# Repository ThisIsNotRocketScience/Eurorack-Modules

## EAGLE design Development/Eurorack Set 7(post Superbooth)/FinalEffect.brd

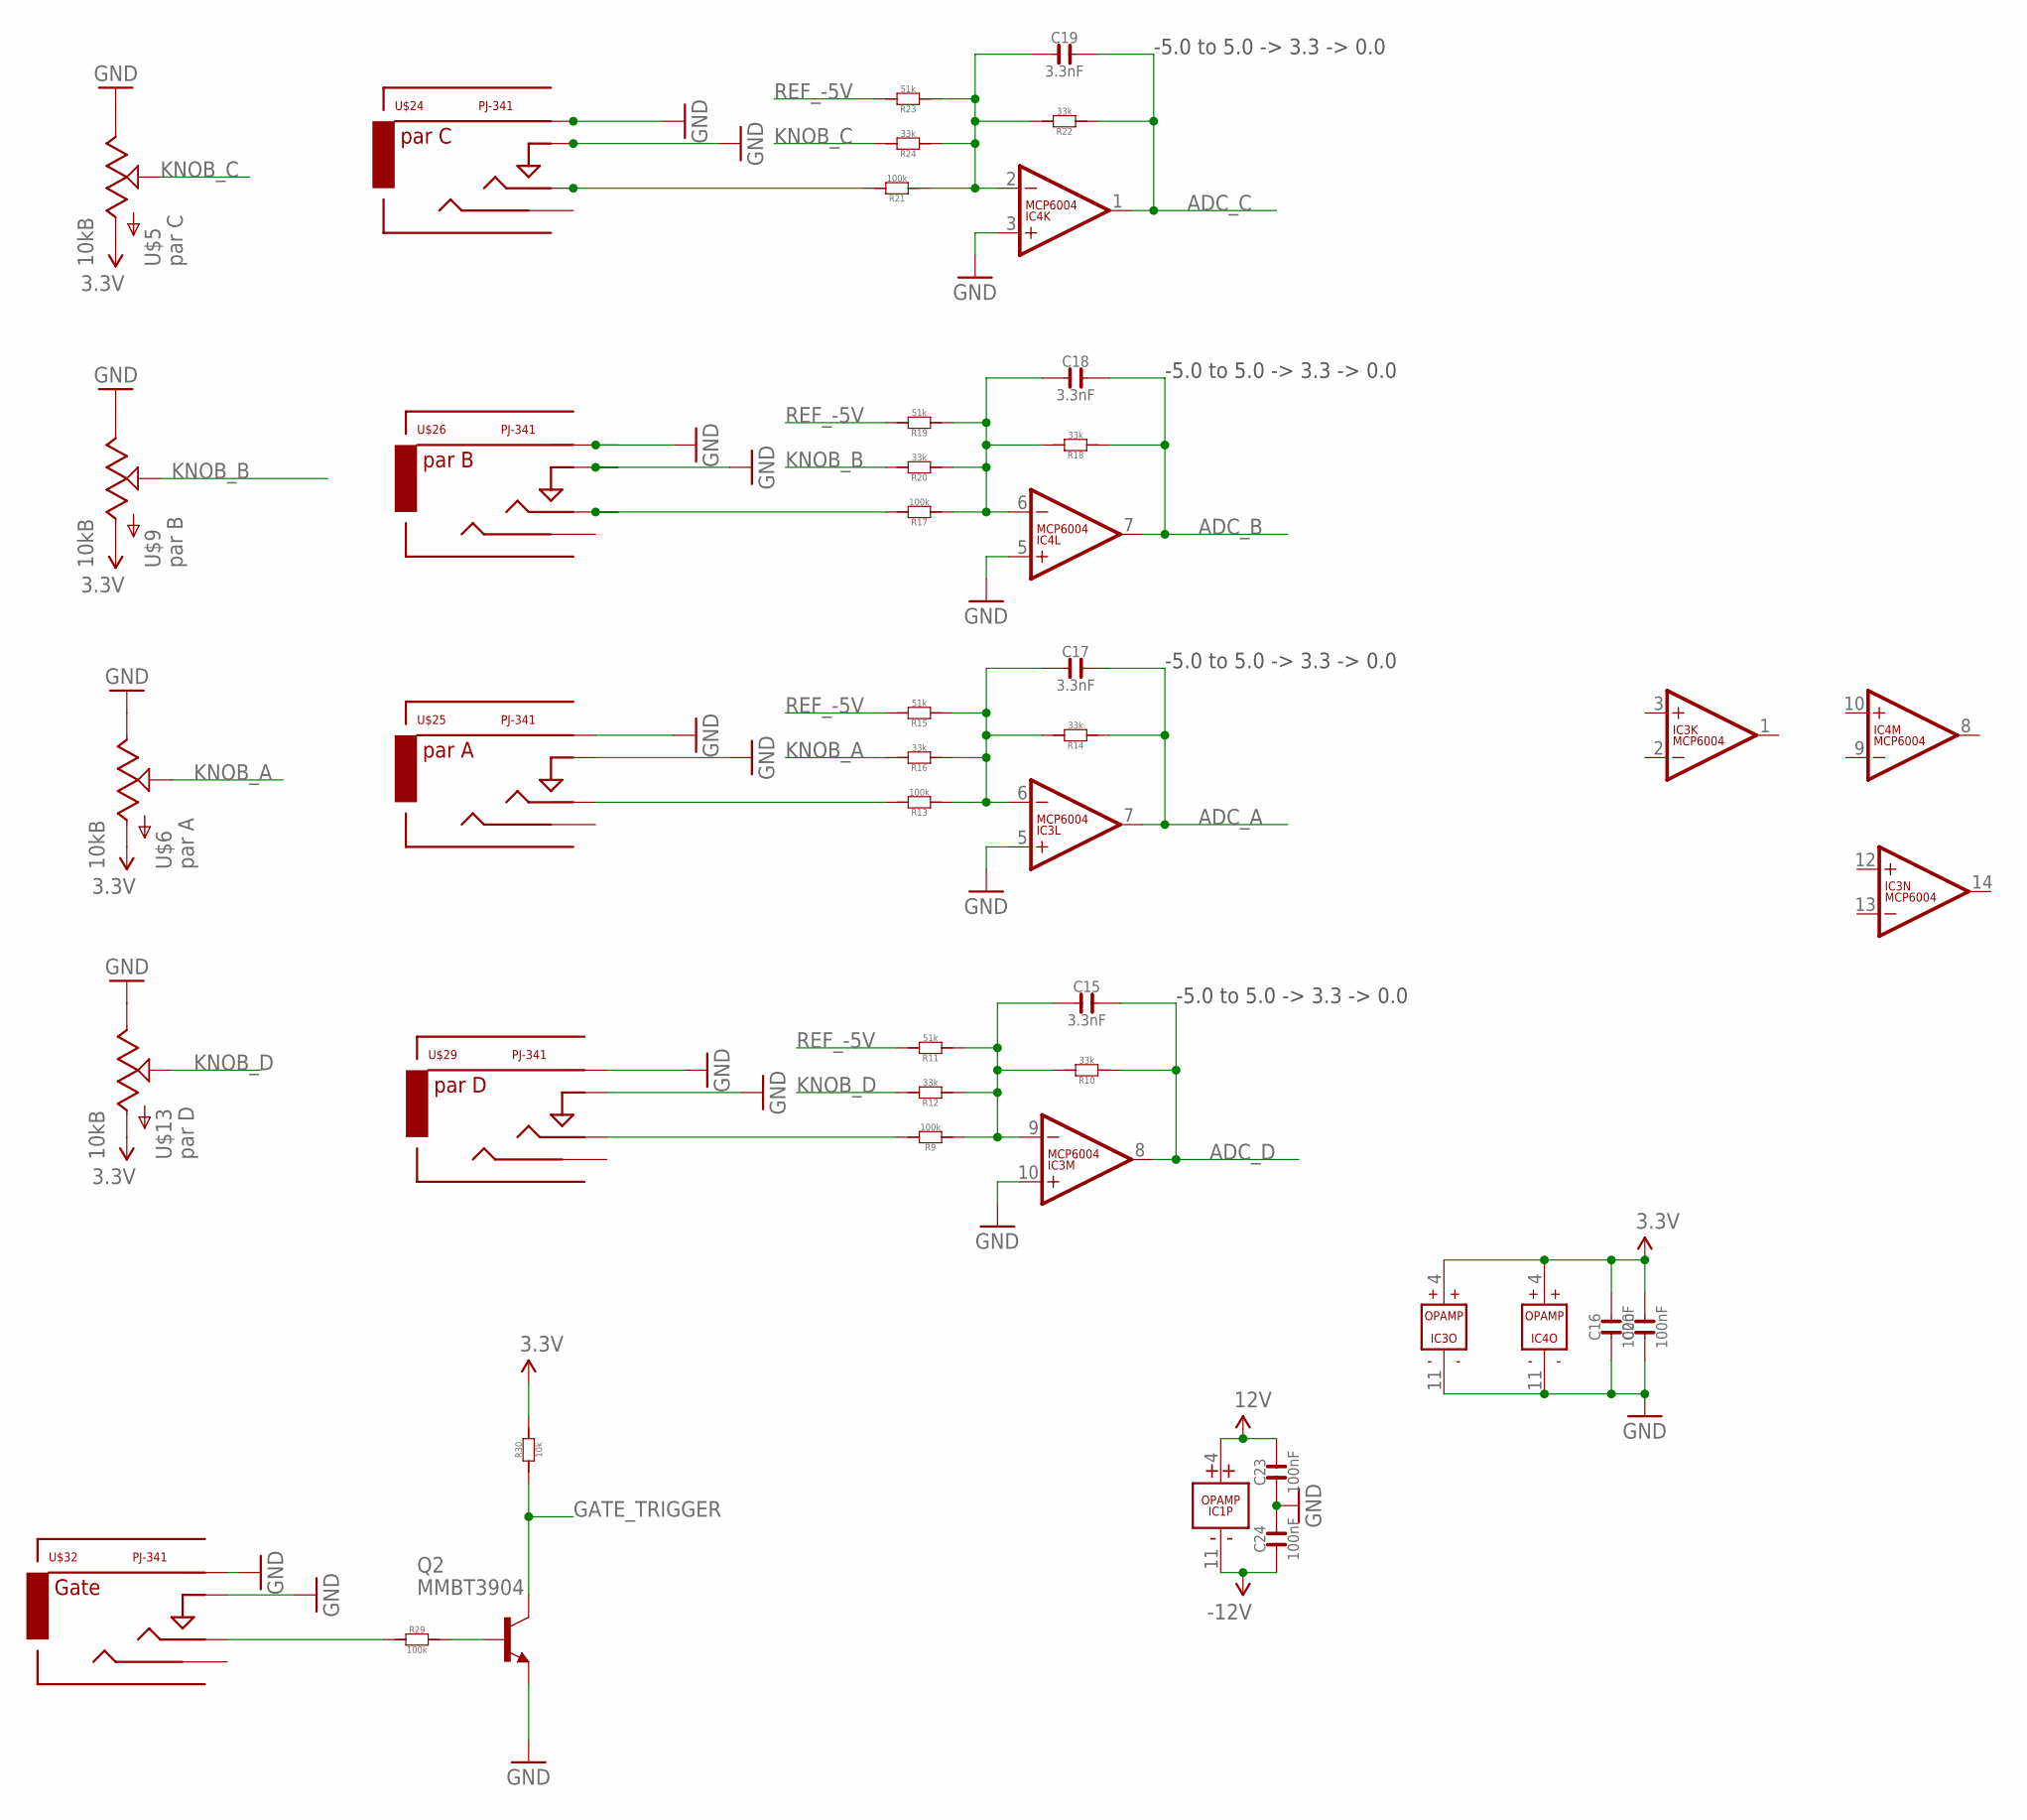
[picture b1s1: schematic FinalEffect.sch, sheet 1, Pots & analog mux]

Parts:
C15, C17, C18, C19: 3.3nF; C0603
C16, C20, C23, C24: 100nF; C0603
IC1: TL074D; SO14
IC3, IC4: MCP6004; SO14; MPN MCP6004-I/SL.
Q2: MMBT3904; SOT23-BEC; MPN PMBT3904,215
R9, R13, R17, R21, R29: 100k; R0603
R10, R12, R14, R16, R18, R20, R22, R24: 33k; R0603
R11, R15, R19, R23: 51k; R0603
R30: 10k; R0603
U$5, U$6, U$9, U$13: 10kB; OG-POTS_ALPS_POT_VERTICAL
U$24, U$25, U$26, U$29, U$32: PJ-341; 3.5MM-JACK-SWITCH-13MM-INPUT

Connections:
3.3V: C16.2, C20.2, IC3.4 (V+), IC4.4 (V+), R30.2, U$5.P$3 (A), U$6.P$3 (A), U$9.P$3 (A), U$13.P$3 (A); also elsewhere on the board
12V: C23.2, IC1.4 (V+); also elsewhere on the board
-12V: C24.1, IC1.11 (V-); also elsewhere on the board
ADC_A: C17.2, IC3.7 (OUT), R14.1; also elsewhere on the board
ADC_B: C18.2, IC4.7 (OUT), R18.1; also elsewhere on the board
ADC_C: C19.2, IC4.1 (OUT), R22.1; also elsewhere on the board
ADC_D: C15.2, IC3.8 (OUT), R10.1; also elsewhere on the board
GATE_TRIGGER: Q2.C, R30.1; also elsewhere on the board
GND: C16.1, C20.1, C23.1, C24.2, IC3.5 (+IN), IC3.10 (+IN), IC3.11 (V-), IC4.3 (+IN), IC4.5 (+IN), IC4.11 (V-), Q2.E, U$5.P$1 (E), U$6.P$1 (E), U$9.P$1 (E), U$13.P$1 (E), U$24.RING@3 (RING), U$24.SWITCH@3 (SWITCH), U$25.RING@3 (RING), U$25.SWITCH@3 (SWITCH), U$26.RING@3 (RING), U$26.SWITCH@3 (SWITCH), U$29.RING@3 (RING), U$29.SWITCH@3 (SWITCH), U$32.RING@3 (RING), U$32.SWITCH@3 (SWITCH); also elsewhere on the board
KNOB_A: R16.2, U$6.P$2 (S)
KNOB_B: R20.2, U$9.P$2 (S)
KNOB_C: R24.2, U$5.P$2 (S)
KNOB_D: R12.2, U$13.P$2 (S)
unnamed: R17.2, U$26.TIP@3 (TIP)
unnamed: C18.1, IC4.6 (-IN), R17.1, R18.2, R19.1, R20.1
unnamed: R21.2, U$24.TIP@3 (TIP)
unnamed: C19.1, IC4.2 (-IN), R21.1, R22.2, R23.1, R24.1
unnamed: Q2.B, R29.2
unnamed: R9.2, U$29.TIP@3 (TIP)
unnamed: C15.1, IC3.9 (-IN), R9.1, R10.2, R11.1, R12.1
unnamed: R13.2, U$25.TIP@3 (TIP)
unnamed: C17.1, IC3.6 (-IN), R13.1, R14.2, R15.1, R16.1
unnamed: R29.1, U$32.TIP@3 (TIP)
REF_-5V: R11.2, R15.2, R19.2, R23.2; also elsewhere on the board

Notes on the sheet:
-5.0 to 5.0 -> 3.3 -> 0.0

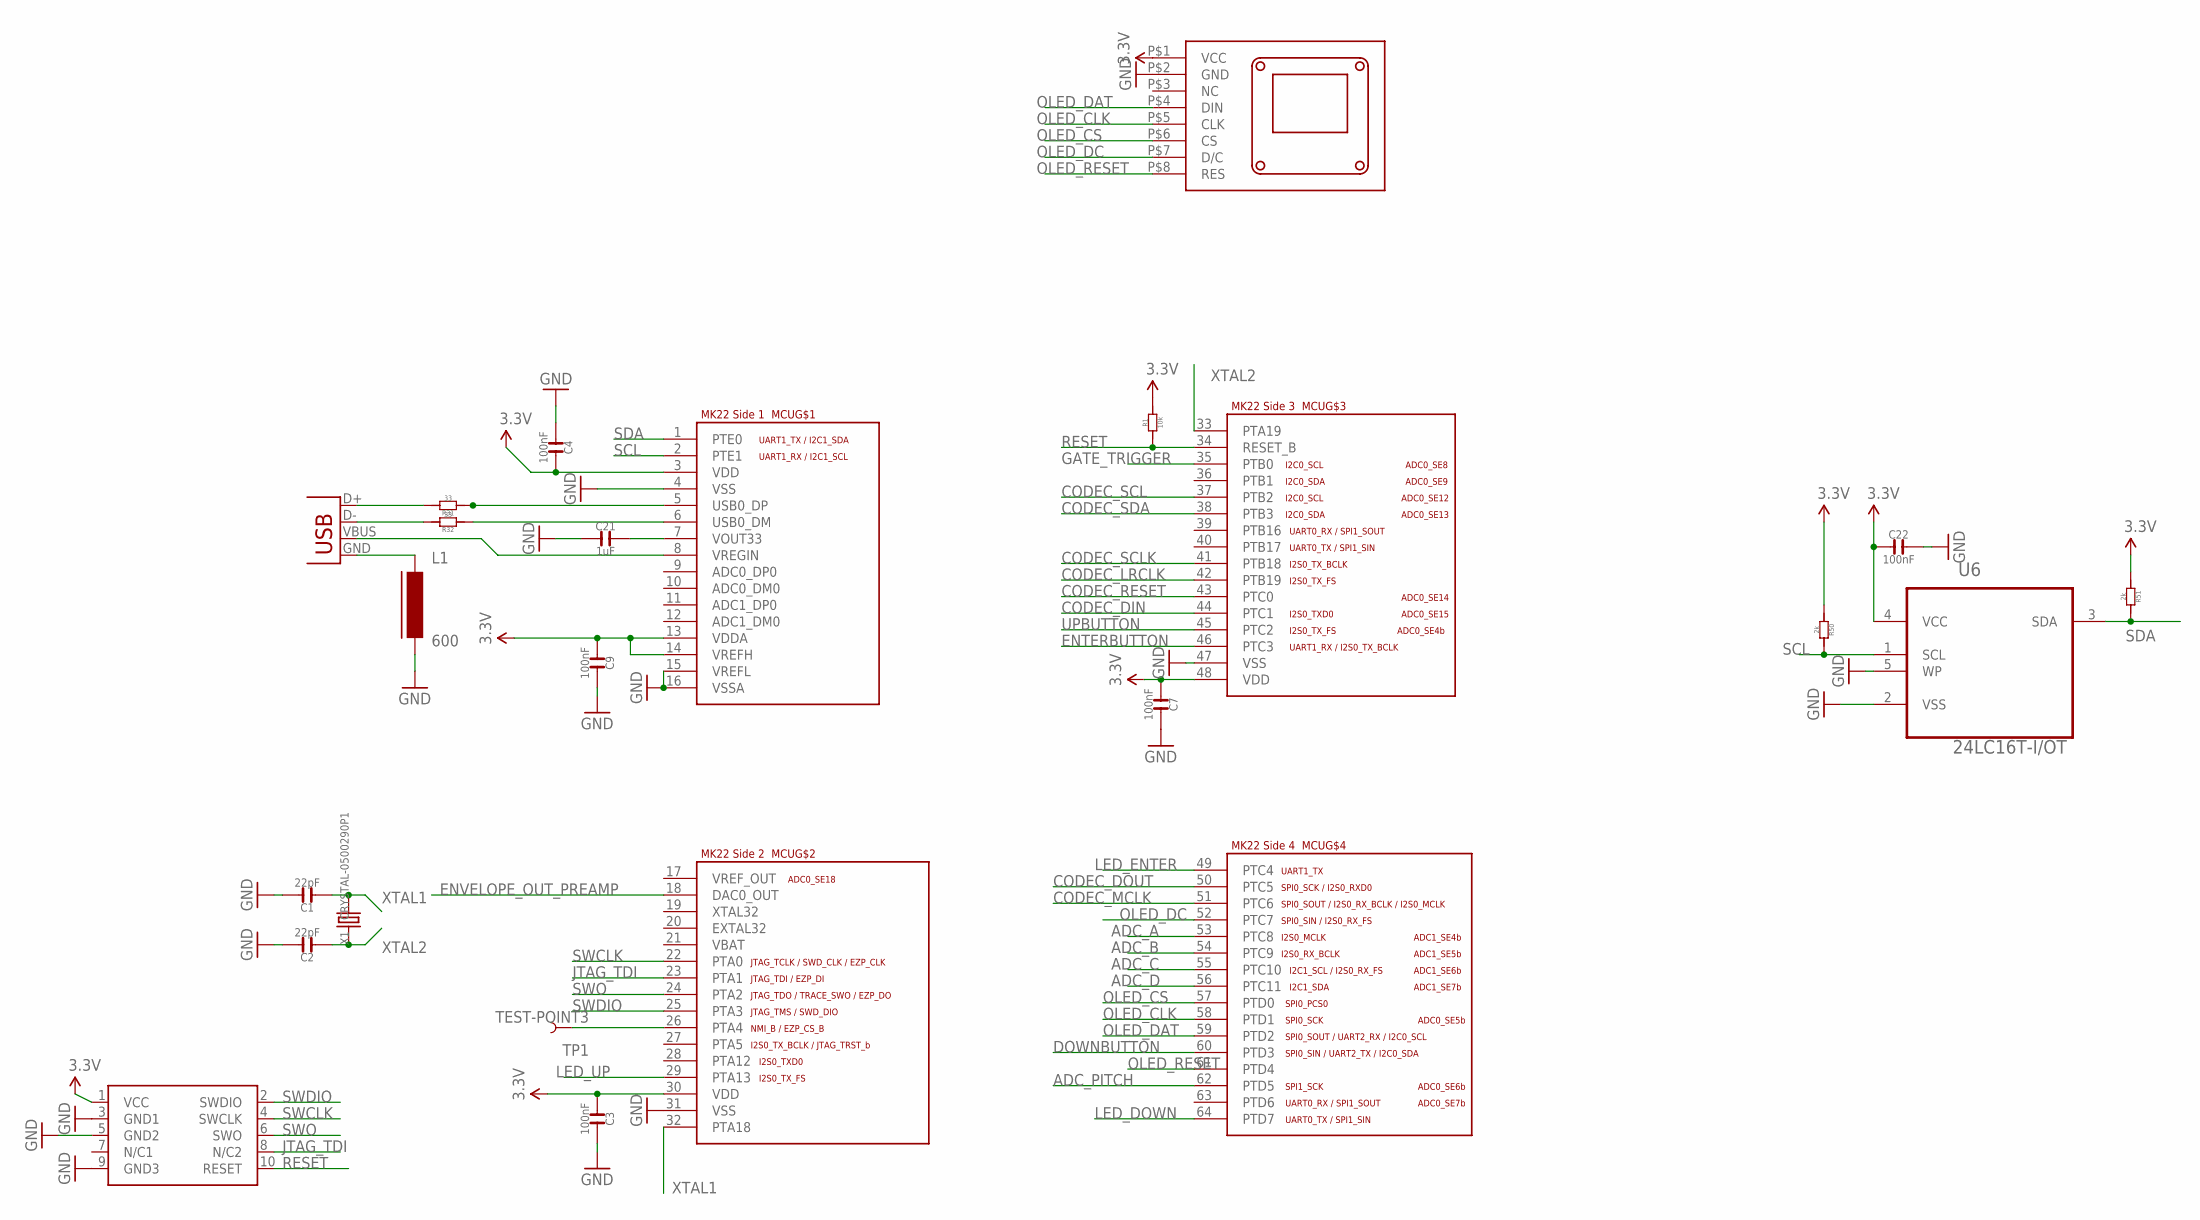
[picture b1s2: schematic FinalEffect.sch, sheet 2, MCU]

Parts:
C1, C2: 22pF; C0603
C3, C4, C7, C9, C22: 100nF; C0603
C21: 1uF; C0603
JP1: USBPTH-VERTICAL; USB-B-PTH-VERTICAL
L1: 600; FB603
MCU: MK22_120_TQFP64; MK22_TQFP64
R1: 10k; R0603
R31, R32: 33; R0603
R50, R51: 2k; R0603
SWD1: CORTEX_SWD; M50-3600542
TP1: TEST-POINT3; PAD.03X.03
U6: 24LC16T-I/OT; SOT95P290X145-5N; MPN 24LC00T-I/OT
U$3: 0.96OLEDMODULE; 1.3"OLEDMODULE
X1: CRYSTAL-0500290P1; 2P-SMD-5.0X3.2

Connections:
3.3V: C3.1, C4.2, C7.1, C9.1, C22.1, MCU.3 (VDD), MCU.13 (VDDA), MCU.14 (VREFH), MCU.30 (VDD), MCU.48 (VDD), R1.2, R50.1, R51.1, SWD1.1 (VCC), U6.4 (VCC), U$3.P$1 (VCC); also elsewhere on the board
ADC_A: MCU.53 (PTC8); also elsewhere on the board
ADC_B: MCU.54 (PTC9); also elsewhere on the board
ADC_C: MCU.55 (PTC10); also elsewhere on the board
ADC_D: MCU.56 (PTC11); also elsewhere on the board
ADC_PITCH: MCU.62 (PTD5); also elsewhere on the board
CODEC_DIN: MCU.44 (PTC1); also elsewhere on the board
CODEC_DOUT: MCU.50 (PTC5); also elsewhere on the board
CODEC_LRCLK: MCU.42 (PTB19); also elsewhere on the board
CODEC_MCLK: MCU.51 (PTC6); also elsewhere on the board
CODEC_RESET: MCU.43 (PTC0); also elsewhere on the board
CODEC_SCL: MCU.37 (PTB2); also elsewhere on the board
CODEC_SCLK: MCU.41 (PTB18); also elsewhere on the board
CODEC_SDA: MCU.38 (PTB3); also elsewhere on the board
DOWNBUTTON: MCU.60 (PTD3); also elsewhere on the board
ENTERBUTTON: MCU.46 (PTC3); also elsewhere on the board
ENVELOPE_OUT_PREAMP: MCU.18 (DAC0_OUT); also elsewhere on the board
GATE_TRIGGER: MCU.35 (PTB0); also elsewhere on the board
GND: C1.2, C2.2, C3.2, C4.1, C7.2, C9.2, C21.1, C22.2, L1.2, MCU.4 (VSS), MCU.15 (VREFL), MCU.16 (VSSA), MCU.31 (VSS), MCU.47 (VSS), SWD1.3 (GND1), SWD1.5 (GND2), SWD1.9 (GND3), U6.2 (VSS), U6.5 (WP), U$3.P$2 (GND); also elsewhere on the board
JTAG_TDI: MCU.23 (PTA1), SWD1.8 (N/C2)
LED_DOWN: MCU.64 (PTD7); also elsewhere on the board
LED_ENTER: MCU.49 (PTC4); also elsewhere on the board
LED_UP: MCU.29 (PTA13); also elsewhere on the board
unnamed: C21.2, MCU.7 (VOUT33)
unnamed: JP1.D+, R31.2
unnamed: JP1.D-, R32.2
unnamed: JP1.VBUS, MCU.8 (VREGIN)
unnamed: MCU.5 (USB0_DP), R31.1
unnamed: MCU.6 (USB0_DM), R32.1
unnamed: JP1.GND, L1.1
unnamed: MCU.26 (PTA4), TP1.P$1
OLED_CLK: MCU.58 (PTD1), U$3.P$5 (CLK)
OLED_CS: MCU.57 (PTD0), U$3.P$6 (CS)
OLED_DAT: MCU.59 (PTD2), U$3.P$4 (DIN)
OLED_DC: MCU.52 (PTC7), U$3.P$7 (D/C)
OLED_RESET: MCU.61 (PTD4), U$3.P$8 (RES)
RESET: MCU.34 (RESET_B), R1.1, SWD1.10 (RESET)
SCL: MCU.2 (PTE1), R50.2, U6.1 (SCL)
SDA: MCU.1 (PTE0), R51.2, U6.3 (SDA)
SWCLK: MCU.22 (PTA0), SWD1.4 (SWCLK)
SWDIO: MCU.25 (PTA3), SWD1.2 (SWDIO)
SWO: MCU.24 (PTA2), SWD1.6 (SWO)
UPBUTTON: MCU.45 (PTC2); also elsewhere on the board
XTAL1: C1.1, MCU.32 (PTA18), X1.2
XTAL2: C2.1, MCU.33 (PTA19), X1.1

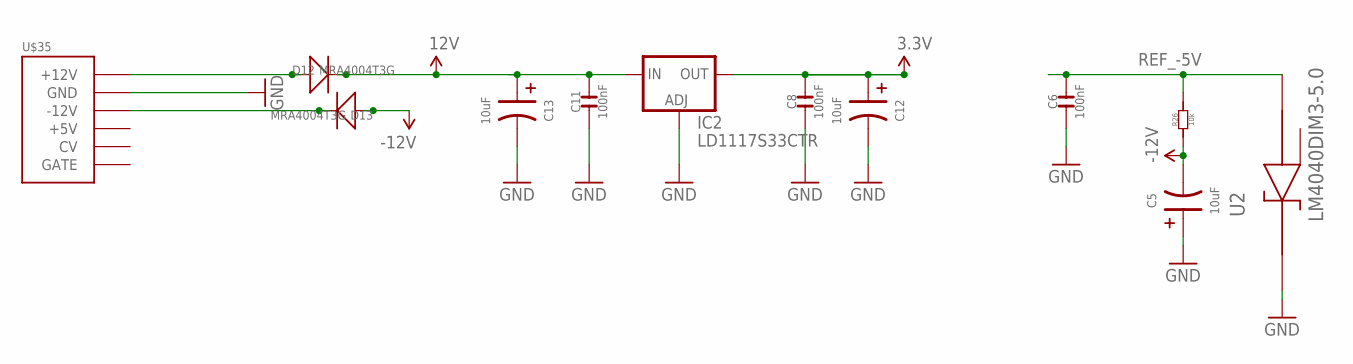
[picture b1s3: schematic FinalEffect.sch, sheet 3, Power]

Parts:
C5, C12, C13: 10uF; CASE-A_3216; MPN TAJB106K020RNJ
C6: 100nF; C0603; MPN 06035C104KAT2A
C8, C11: 100nF; C0603; MPN MC0603F104Z160CT
D12, D13: MRA4004T3G; DO-214AC; MPN US1G-E3/5AT
IC2: LD1117S33CTR; SOT223; MPN LD1117AS33TR
R26: 10k; R0603
U2: LM4040DIM3-5.0; SOT95P237X112-3N
U$35: POWERSMT; 2X08_SMT_HEADER

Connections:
3.3V: C8.2, C12.+ (1), IC2.2 (OUT), IC2.4 (OUT); also elsewhere on the board
12V: C11.2, C13.+ (1), D12.2 (-), IC2.3 (IN); also elsewhere on the board
-12V: C5.- (2), D13.1 (+), R26.1; also elsewhere on the board
GND: C5.+ (1), C6.1, C8.1, C11.1, C12.- (2), C13.- (2), IC2.1 (ADJ), U2.1 (CATHODE), U$35.3 (GND), U$35.4 (GND), U$35.5 (GND), U$35.6 (GND), U$35.7 (GND), U$35.8 (GND); also elsewhere on the board
unnamed: D12.1 (+), U$35.9 (+12V), U$35.10 (+12V)
unnamed: D13.2 (-), U$35.1 (-12V), U$35.2 (-12V)
REF_-5V: C6.2, R26.2, U2.2 (ANODE); also elsewhere on the board

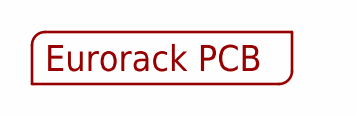
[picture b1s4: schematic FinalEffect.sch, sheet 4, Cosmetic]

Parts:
U$1: EURORACK_PCB12HP; EURORACK12HPPCB

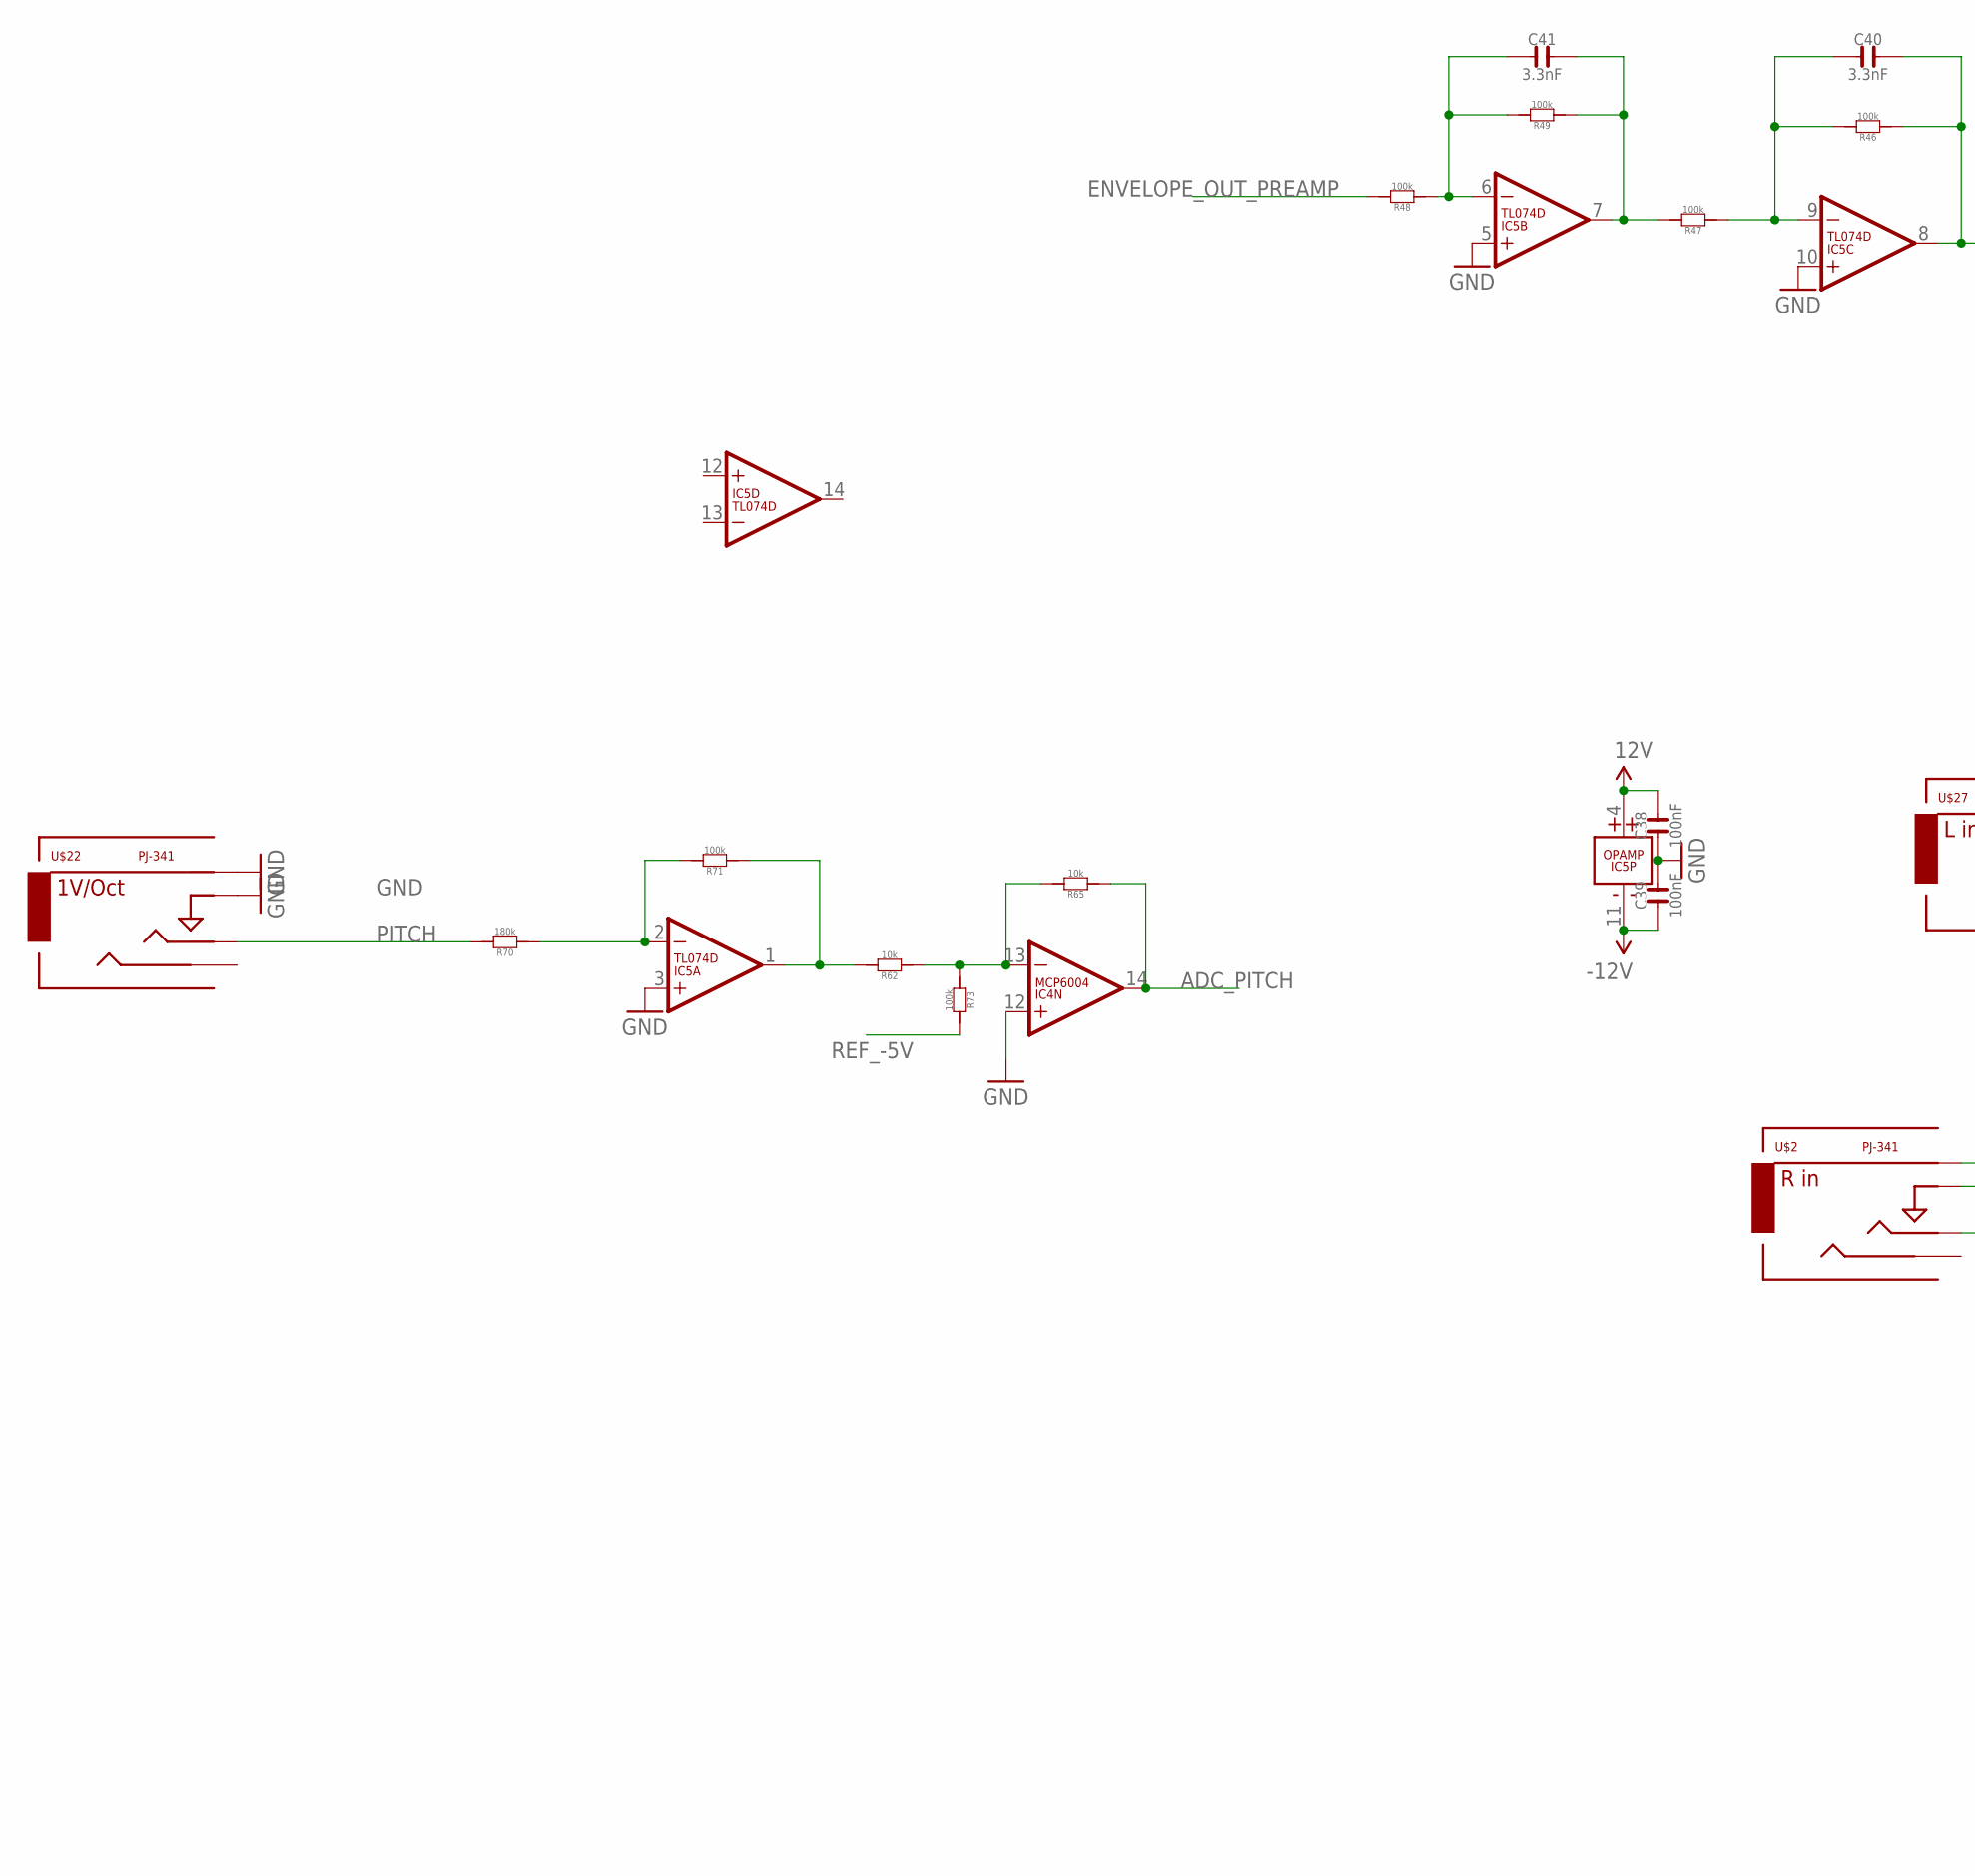
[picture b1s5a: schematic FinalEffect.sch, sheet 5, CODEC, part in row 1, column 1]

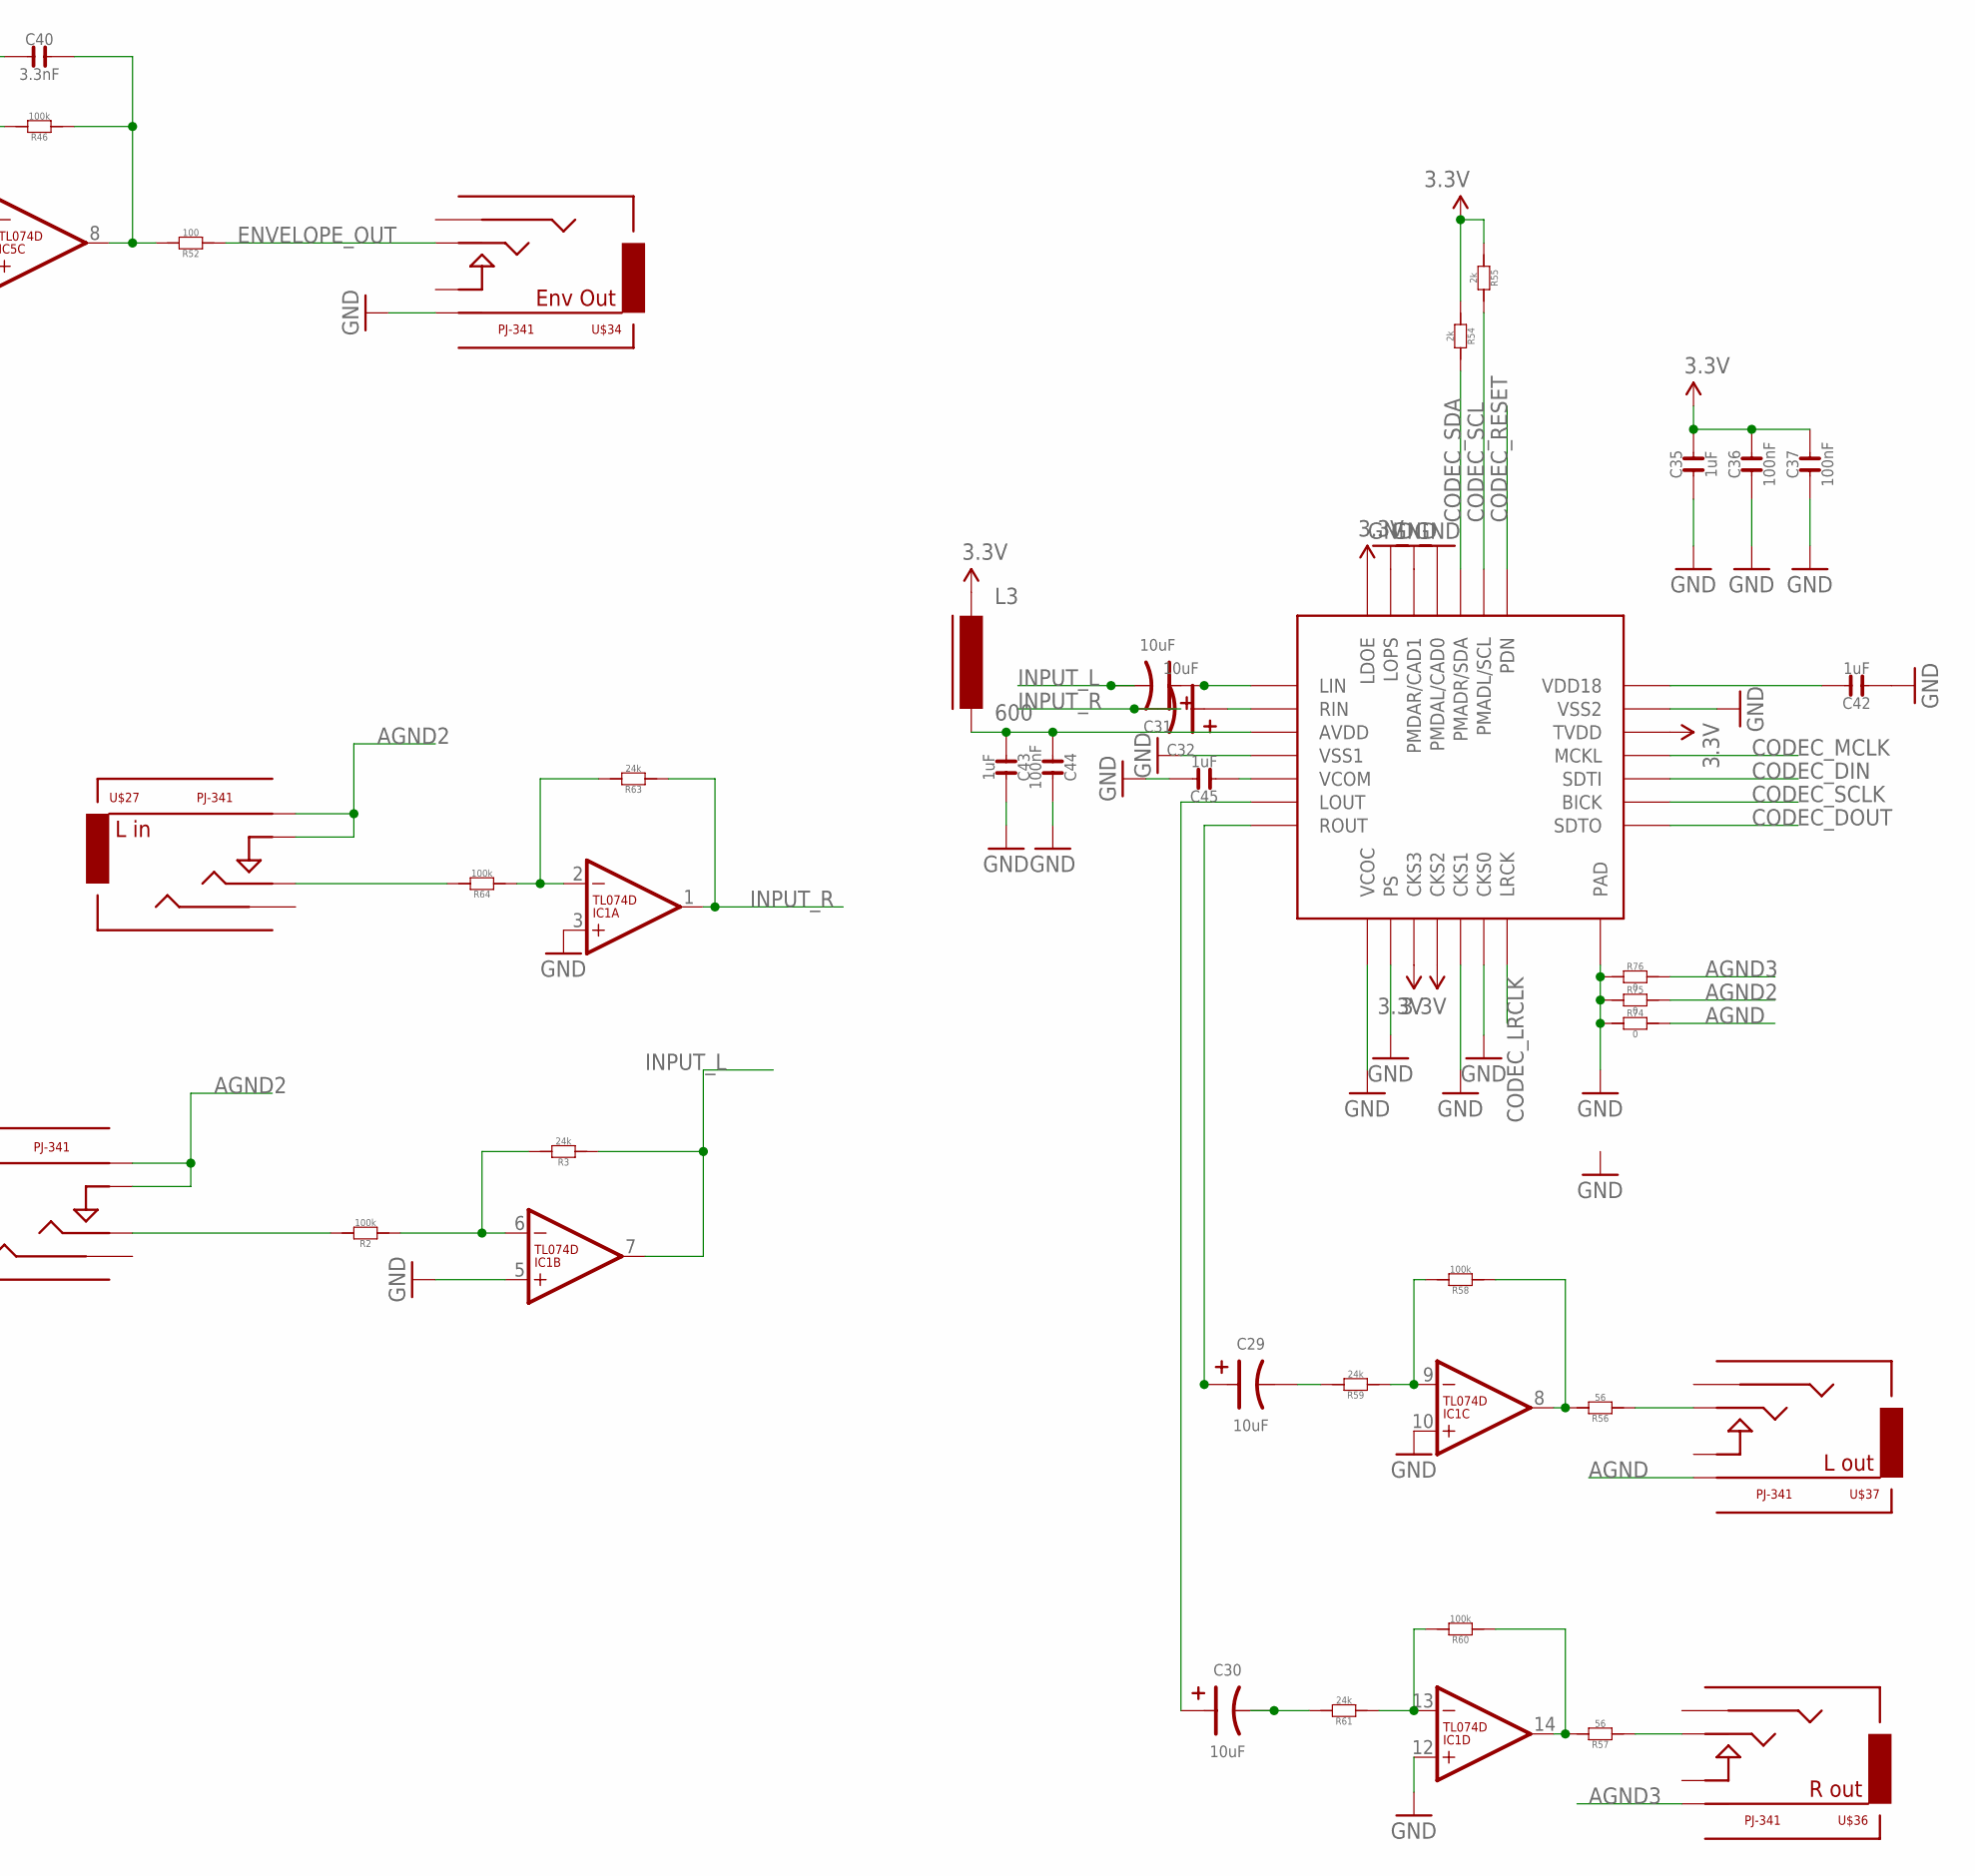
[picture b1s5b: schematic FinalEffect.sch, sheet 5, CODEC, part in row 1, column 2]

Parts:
C29, C30, C31, C32: 10uF; CASE-A_3216; MPN TAJB106K020RNJ
C35, C42, C43, C45: 1uF; C0603
C36, C37, C38, C39, C44: 100nF; C0603
C40, C41: 3.3nF; C0603
IC1, IC5: TL074D; SO14
IC4: MCP6004; SO14; MPN MCP6004-I/SL.
L3: 600; FB603
R2, R46, R47, R48, R49, R58, R60, R64, R71, R73: 100k; R0603
R3, R59, R61, R63: 24k; R0603
R52: 100; R0603
R54, R55: 2k; R0603
R56, R57: 56; R0603
R62, R65: 10k; R0603
R70: 180k; R0603
R74, R75, R76: 0; R0603
U$2, U$22, U$27: PJ-341; 3.5MM-JACK-SWITCH-13MM-INPUT
U$34, U$36, U$37: PJ-341; 3.5MM-JACK-SWITCH-13MM-OUTPUT
U$48: AK4558; QFN28

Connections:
3.3V: C35.2, C36.2, C37.2, L3.1, R54.2, R55.2, U$48.P$3 (CKS3), U$48.P$4 (CKS2), U$48.P$12 (TVDD), U$48.P$21 (LDOE); also elsewhere on the board
3.3VAUDIO1: C43.1, C44.1, L3.2, U$48.P$24 (AVDD)
12V: C38.2, IC5.4 (V+); also elsewhere on the board
-12V: C39.1, IC5.11 (V-); also elsewhere on the board
ADC_PITCH: IC4.14 (OUT), R65.1; also elsewhere on the board
AGND: R74.1, U$37.RING@3 (RING)
AGND2: R75.1, U$2.RING@3 (RING), U$2.SWITCH@3 (SWITCH), U$27.RING@3 (RING), U$27.SWITCH@3 (SWITCH)
AGND3: R76.1, U$36.RING@3 (RING)
CODEC_DIN: U$48.P$10 (SDTI); also elsewhere on the board
CODEC_DOUT: U$48.P$8 (SDTO); also elsewhere on the board
CODEC_LRCLK: U$48.P$7 (LRCK); also elsewhere on the board
CODEC_MCLK: U$48.P$11 (MCKL); also elsewhere on the board
CODEC_RESET: U$48.P$15 (PDN); also elsewhere on the board
CODEC_SCL: R55.1, U$48.P$16 (PMADL/SCL); also elsewhere on the board
CODEC_SCLK: U$48.P$9 (BICK); also elsewhere on the board
CODEC_SDA: R54.1, U$48.P$17 (PMADR/SDA); also elsewhere on the board
ENVELOPE_OUT: R52.1, U$34.TIP@3 (TIP)
ENVELOPE_OUT_PREAMP: R48.2; also elsewhere on the board
GND: C35.1, C36.1, C37.1, C38.1, C39.2, C42.1, C43.2, C44.2, C45.2, IC1.3 (+IN), IC1.5 (+IN), IC1.10 (+IN), IC1.12 (+IN), IC4.12 (+IN), IC5.3 (+IN), IC5.5 (+IN), IC5.10 (+IN), R74.2, R75.2, R76.2, U$22.RING@3 (RING), U$22.SWITCH@3 (SWITCH), U$34.RING@3 (RING), U$48.P$1 (VCOC), U$48.P$2 (PS), U$48.P$5 (CKS1), U$48.P$6 (CKS0), U$48.P$13 (VSS2), U$48.P$18 (PMDAL/CAD0), U$48.P$19 (PMDAR/CAD1), U$48.P$20 (LOPS), U$48.P$25 (VSS1), U$48.PAD; also elsewhere on the board
INPUT_L: C31.- (2), IC1.7 (OUT), R3.1
INPUT_R: C32.- (2), IC1.1 (OUT), R63.1
LEFT_AFTER_CAP: C29.- (2), R59.2
LEFT_BEFORE_CAP: C29.+ (1), U$48.P$28 (ROUT)
LEFT_POST_OPAMP: IC1.8 (OUT), R56.2, R58.1
LEFT_PRE_OPAMP: IC1.9 (-IN), R58.2, R59.1
LEFT_TO_JACK: R56.1, U$37.TIP@3 (TIP)
unnamed: R2.2, U$2.TIP@3 (TIP)
unnamed: IC1.6 (-IN), R2.1, R3.2
unnamed: C40.2, IC5.8 (OUT), R46.1, R52.2
unnamed: C32.+ (1), U$48.P$23 (RIN)
unnamed: C41.1, IC5.6 (-IN), R48.1, R49.2
unnamed: C41.2, IC5.7 (OUT), R47.2, R49.1
unnamed: C40.1, IC5.9 (-IN), R46.2, R47.1
unnamed: C30.+ (1), U$48.P$27 (LOUT)
unnamed: C31.+ (1), U$48.P$22 (LIN)
unnamed: R64.2, U$27.TIP@3 (TIP)
unnamed: IC5.2 (-IN), R70.1, R71.2
unnamed: IC5.1 (OUT), R62.2, R71.1
unnamed: C30.- (2), R61.2
unnamed: IC1.14 (OUT), R57.2, R60.1
unnamed: IC1.13 (-IN), R60.2, R61.1
unnamed: R57.1, U$36.TIP@3 (TIP)
unnamed: IC1.2 (-IN), R63.2, R64.1
unnamed: IC4.13 (-IN), R62.1, R65.2, R73.1
unnamed: C42.2, U$48.P$14 (VDD18)
unnamed: C45.1, U$48.P$26 (VCOM)
PITCH: R70.2, U$22.TIP@3 (TIP)
REF_-5V: R73.2; also elsewhere on the board

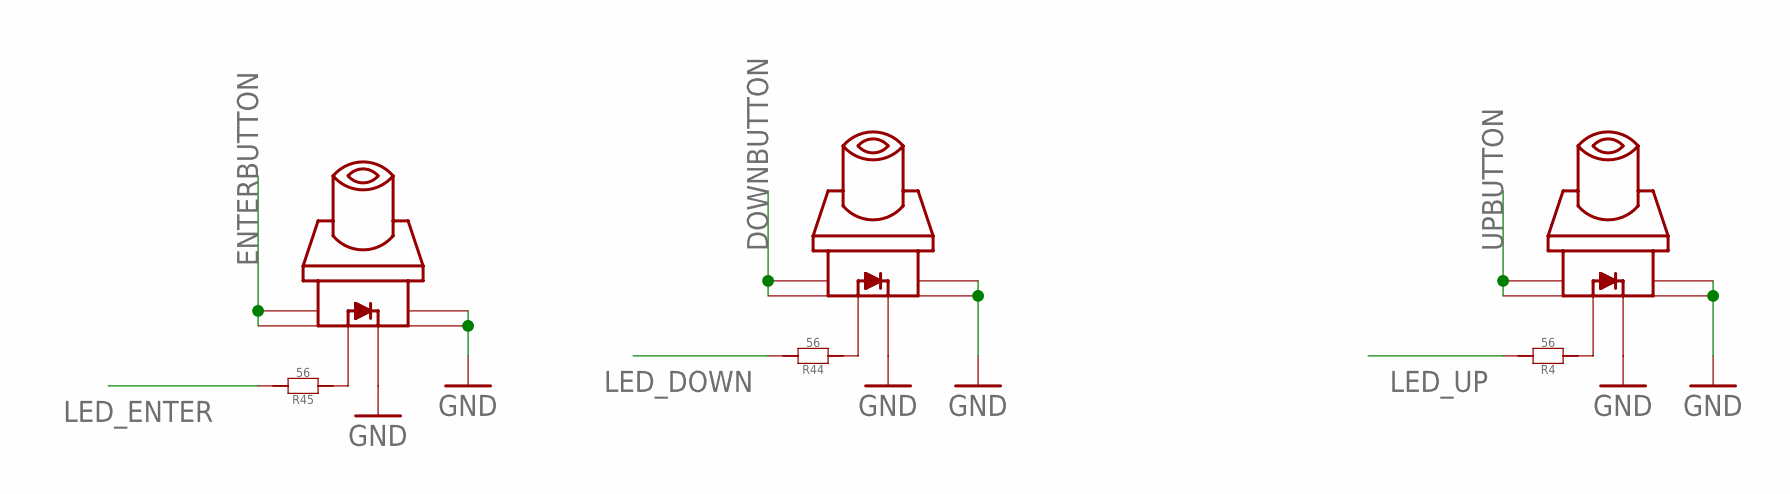
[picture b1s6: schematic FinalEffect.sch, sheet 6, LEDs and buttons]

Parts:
R4, R44, R45: 56; R0603
U$4, U$38, U$39: SWITCH_W_LED_PB6149L-X-102YELLOW; PB6149L

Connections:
DOWNBUTTON: U$38.1, U$38.2; also elsewhere on the board
ENTERBUTTON: U$39.1, U$39.2; also elsewhere on the board
GND: U$4.3, U$4.4, U$4.LEDNEG (NEG), U$38.3, U$38.4, U$38.LEDNEG (NEG), U$39.3, U$39.4, U$39.LEDNEG (NEG); also elsewhere on the board
LED_DOWN: R44.2; also elsewhere on the board
LED_ENTER: R45.2; also elsewhere on the board
LED_UP: R4.2; also elsewhere on the board
unnamed: R4.1, U$4.LEDPOS (POS)
unnamed: R44.1, U$38.LEDPOS (POS)
unnamed: R45.1, U$39.LEDPOS (POS)
UPBUTTON: U$4.1, U$4.2; also elsewhere on the board

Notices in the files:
parts and their libraries:
SparkFun-Aesthetics: Licensing: CC v3.0 Share-Alike You are welcome to use this library for commercial purposes.
